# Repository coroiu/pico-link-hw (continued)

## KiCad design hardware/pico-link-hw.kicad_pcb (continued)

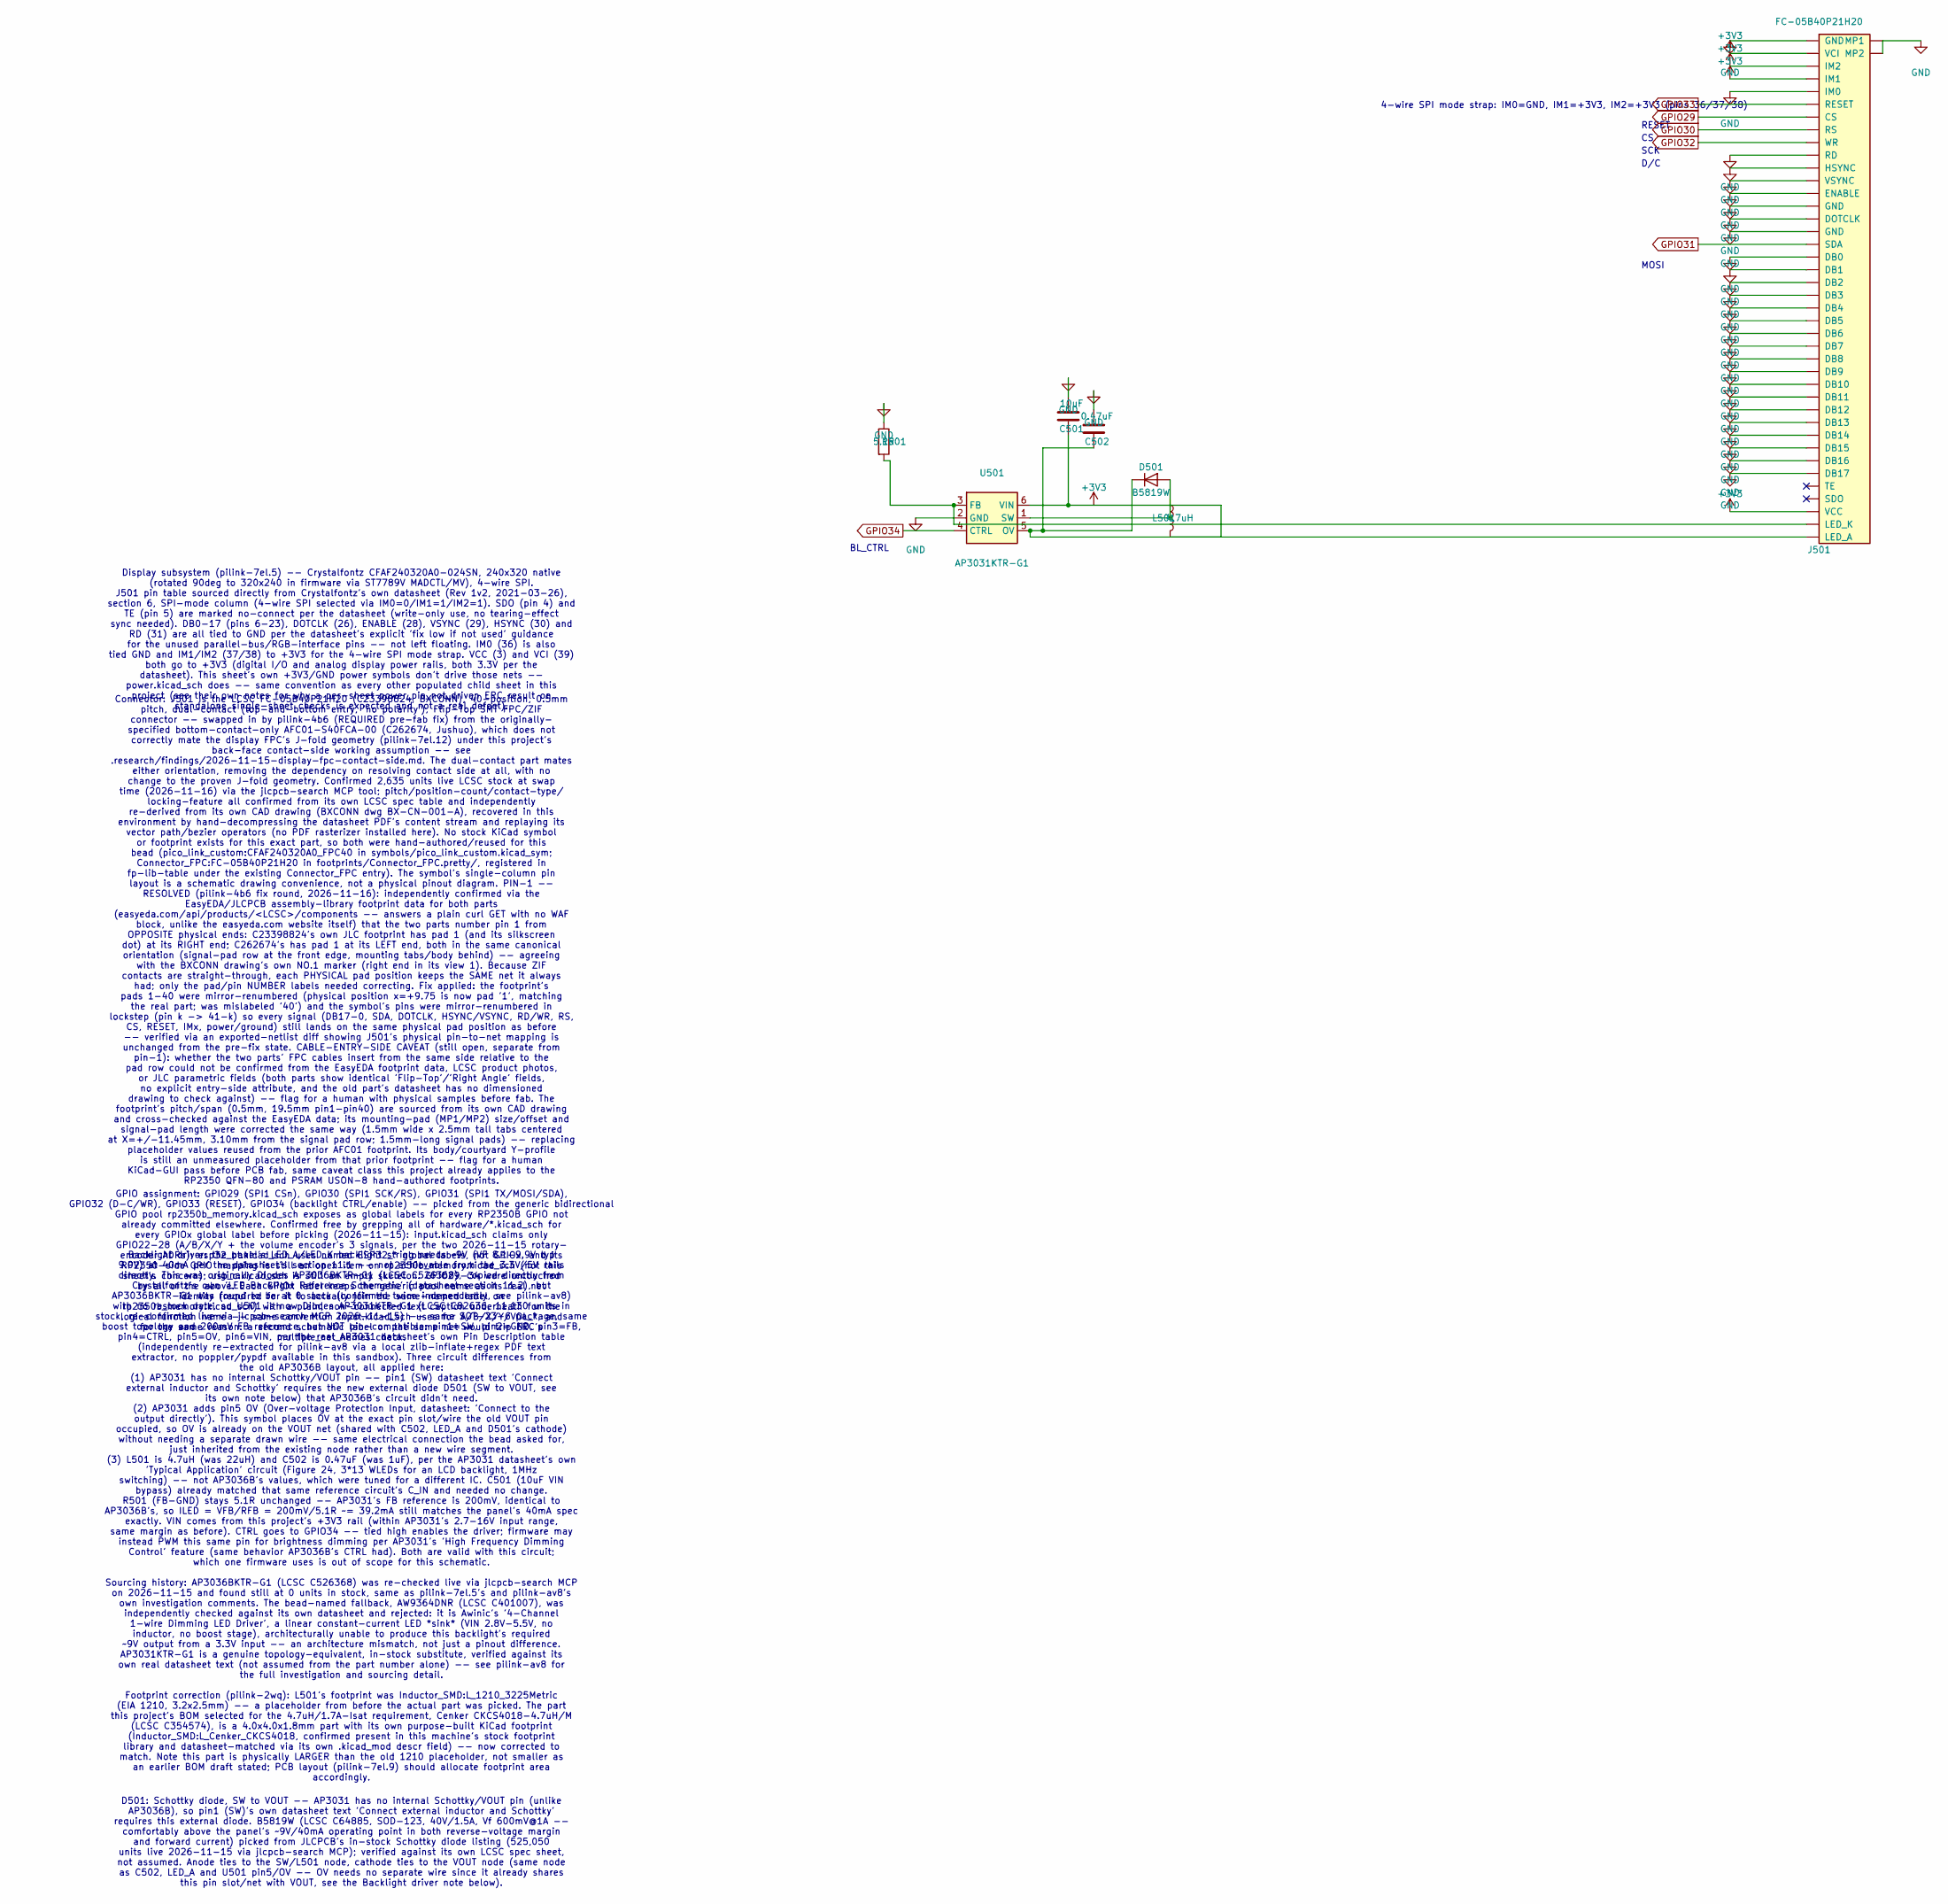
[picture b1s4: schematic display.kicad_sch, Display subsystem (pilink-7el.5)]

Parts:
C501: 10uF; C_0805_2012Metric
C502: 0.47uF; C_0805_2012Metric
D501: B5819W; D_SOD-123
J501: FC-05B40P21H20
L501: 4.7uH; L_Cenker_CKCS4018
R501: 5.1R; R_0402_1005Metric
U501: AP3031KTR-G1; SOT-23-6

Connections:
+3V3: C501.2, J501.2 (VCI), J501.3 (IM2), J501.4 (IM1), J501.38 (VCC), L501.2, U501.6 (VIN); also elsewhere on the board
GND: C501.1, C502.1, J501.1 (GND), J501.5 (IM0), J501.10 (RD), J501.11 (HSYNC), J501.12 (VSYNC), J501.13 (ENABLE), J501.14 (GND), J501.15 (DOTCLK), J501.16 (GND), J501.18 (DB0), J501.19 (DB1), J501.20 (DB2), J501.21 (DB3), J501.22 (DB4), J501.23 (DB5), J501.24 (DB6), J501.25 (DB7), J501.26 (DB8), J501.27 (DB9), J501.28 (DB10), J501.29 (DB11), J501.30 (DB12), J501.31 (DB13), J501.32 (DB14), J501.33 (DB15), J501.34 (DB16), J501.35 (DB17), J501.MP1, J501.MP2, R501.1, U501.2 (GND); also elsewhere on the board
GPIO29: J501.7 (CS); also elsewhere on the board
GPIO30: J501.8 (RS); also elsewhere on the board
GPIO31: J501.17 (SDA); also elsewhere on the board
GPIO32: J501.9 (WR); also elsewhere on the board
GPIO33: J501.6 (RESET); also elsewhere on the board
GPIO34: U501.4 (CTRL); also elsewhere on the board
unnamed: D501.2 (A), L501.1, U501.1 (SW)
unnamed: C502.2, D501.1 (K), J501.40 (LED_A), U501.5 (OV)
unnamed: J501.39 (LED_K), R501.2, U501.3 (FB)

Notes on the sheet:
MOSI
D/C
SCK
RESET
D501: Schottky diode, SW to VOUT -- AP3031 has no internal Schottky/VOUT pin (unlike AP3036B), so pin1 (SW)'s own datasheet text 'Connect external inductor and Schottky' requires this external diode. B5819W (LCSC C64885, SOD-123, 40V/1.5A, Vf 600mV@1A -- comfortably above the panel's ~9V/40mA opera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
BL_CTRL
4-wire SPI mode strap: IM0=GND, IM1=+3V3, IM2=+3V3 (pins 36/37/38)
Display subsystem (pilink-7el.5) -- Crystalfontz CFAF240320A0-024SN, 240x320 native (rotated 90deg to 320x240 in firmware via ST7789V MADCTL/MV), 4-wire SPI. J501 pin table sourced directly from Crystalfontz's own datasheet (Rev 1v2, 2021-03-26), section 6, SPI-mode column (4-wire SPI selected via 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
Connector: J501 is the LCSC FC-05B40P21H20 (C23398824, BXCONN), 40-position, 0.5mm pitch, dual-contact (top-and-bottom entry, 'no polarity'), Flip-Top SMT FPC/ZIF connector -- swapped in by pilink-4b6 (REQUIRED pre-fab fix) from the originally- specified bottom-contact-only AFC01-S40FCA-00 (C262674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
GPIO assignment: GPIO29 (SPI1 CSn), GPIO30 (SPI1 SCK/RS), GPIO31 (SPI1 TX/MOSI/SDA), GPIO32 (D-C/WR), GPIO33 (RESET), GPIO34 (backlight CTRL/enable) -- picked from the generic bidirectional GPIO pool rp2350b_memory.kicad_sch exposes as global labels for every RP2350B GPIO not already committed else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
Backlight driver: the panel's LED_A/LED_K backlight string needs ~9V (VF 8.1-9.9V typ 9.0V) at 40mA per the datasheet's section 11.1 -- not achievable from the 3.3V/5V rails directly. This was originally Diodes AP3036BKTR-G1 (LCSC C526368), copied directly from Crystalfontz's own 'LED Backlight Ref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

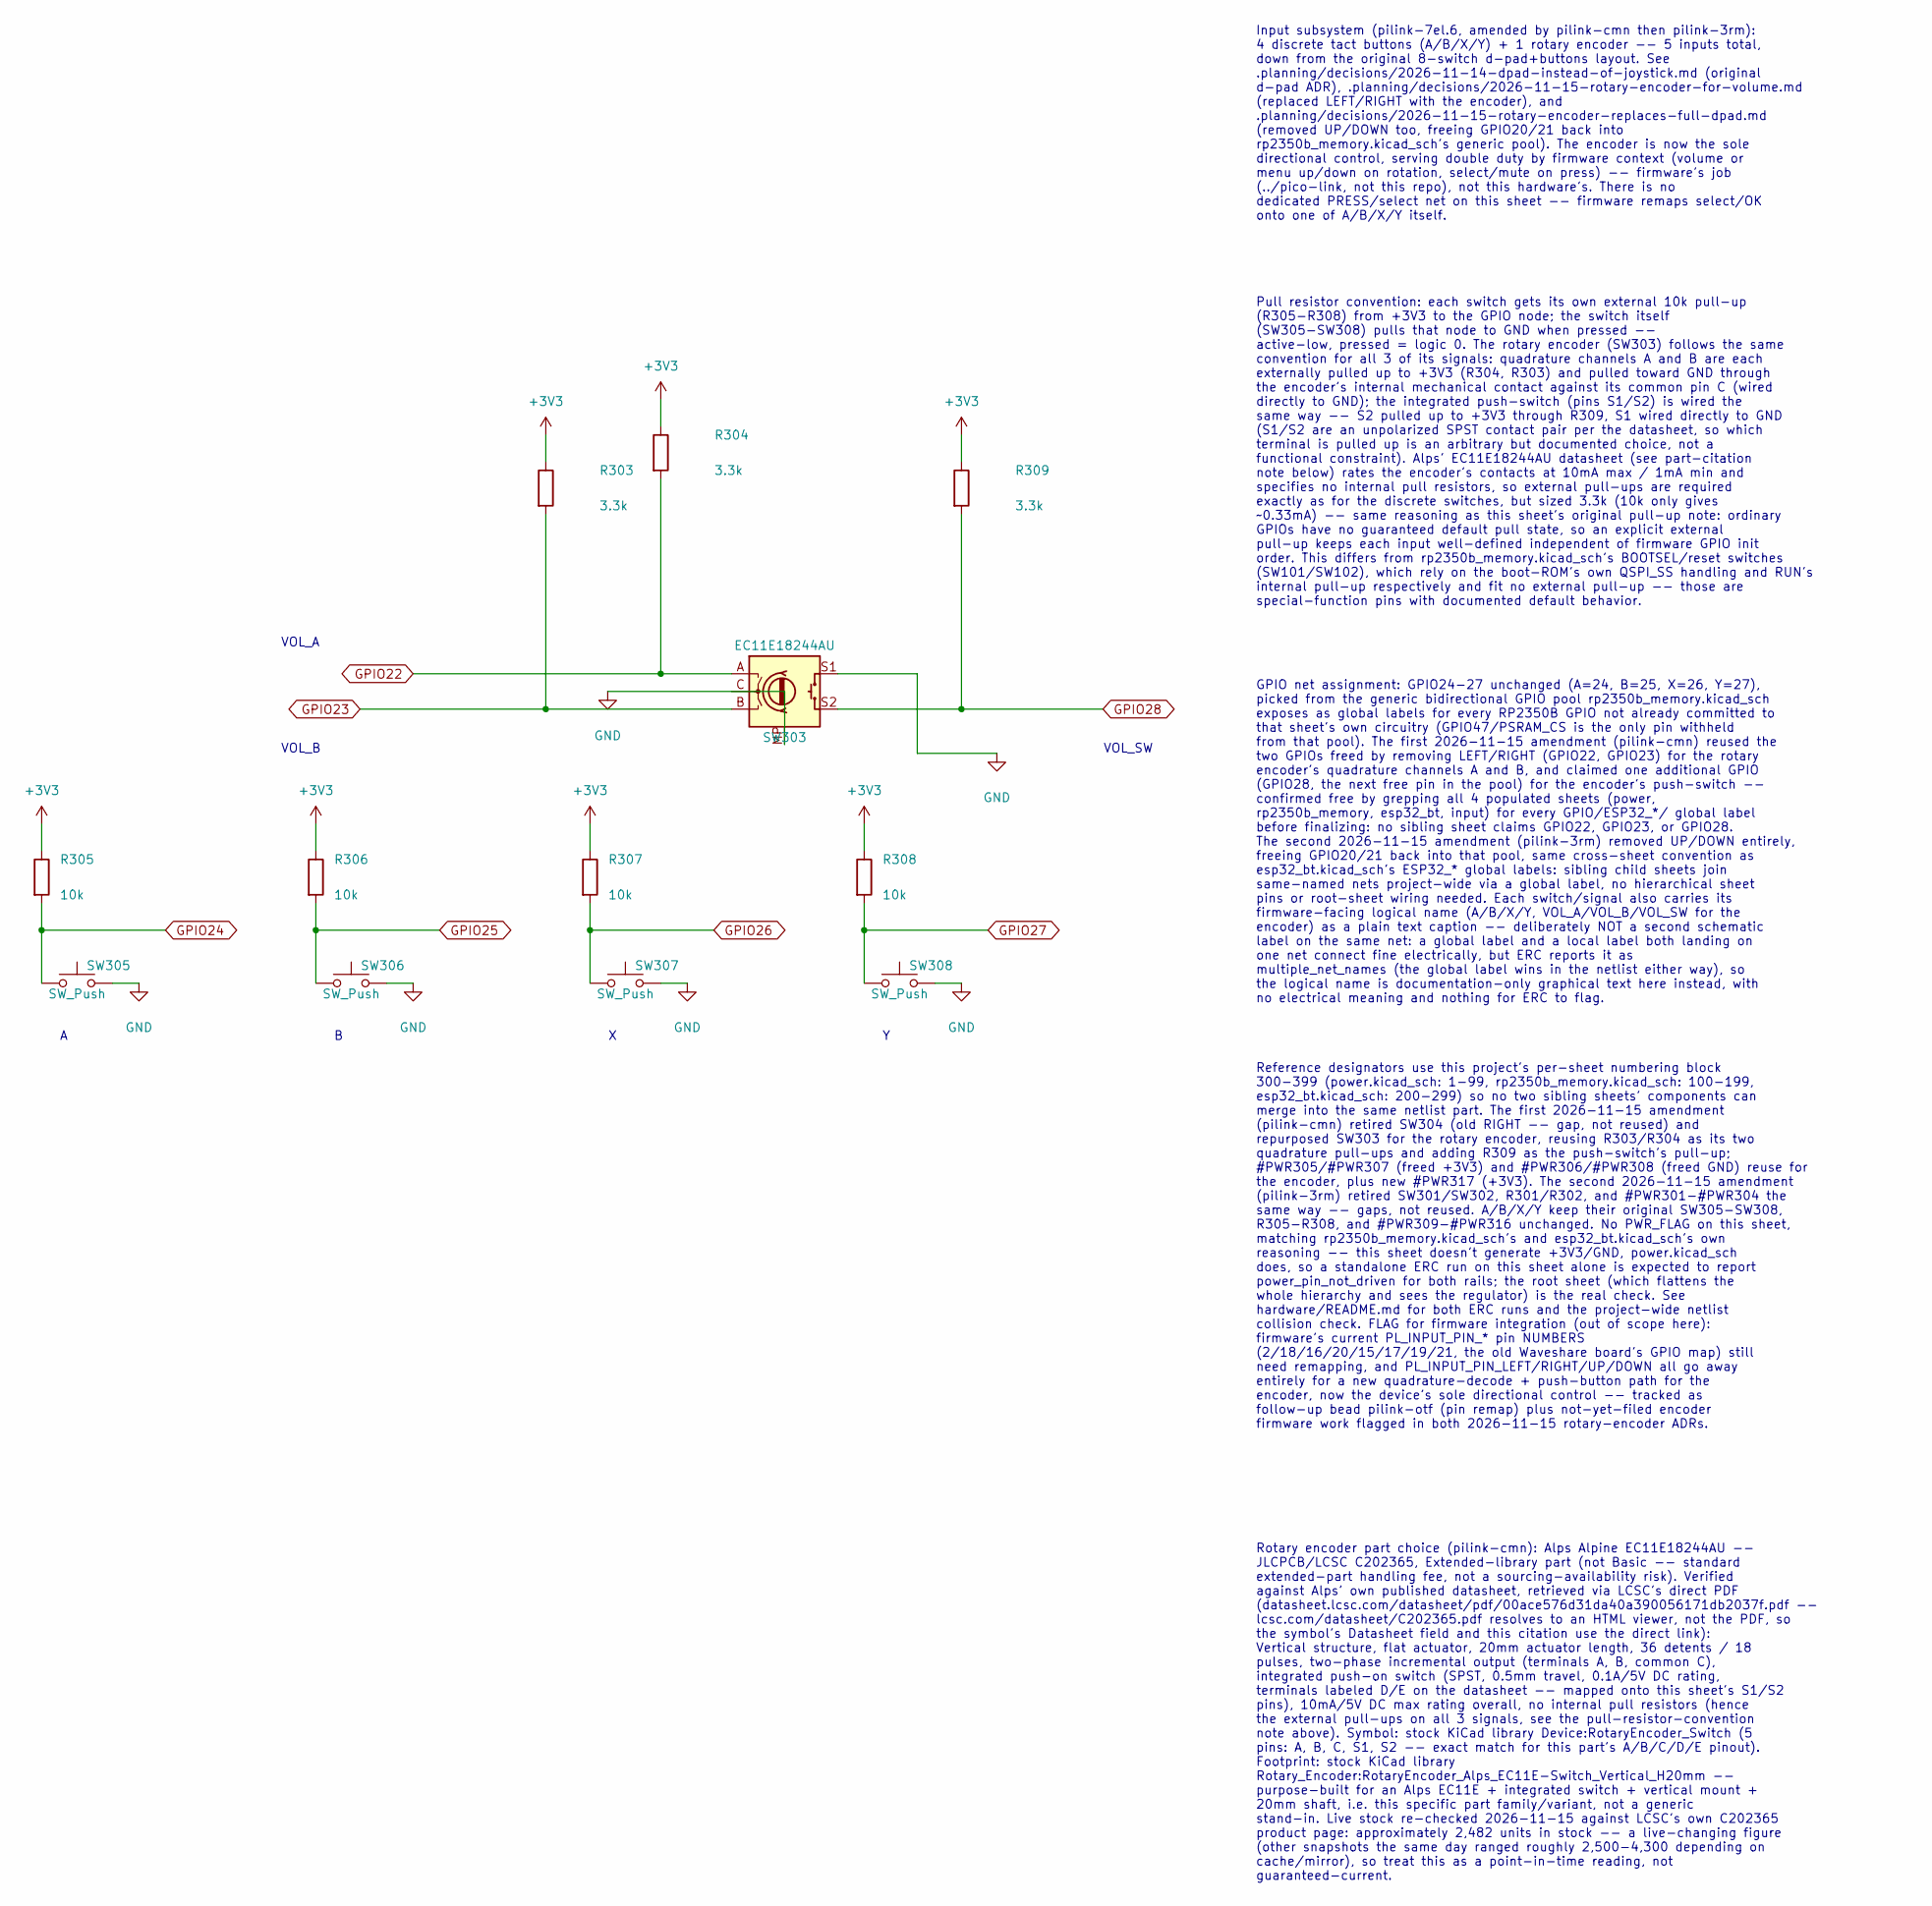
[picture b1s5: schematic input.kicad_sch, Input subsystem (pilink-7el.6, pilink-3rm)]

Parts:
R303, R304, R309: 3.3k; R_0402_1005Metric
R305, R306, R307, R308: 10k; R_0402_1005Metric
SW303: EC11E18244AU; RotaryEncoder_Alps_EC11E-Switch_Vertical_H20mm
SW305, SW306, SW307, SW308: SW_Push; SW_SPST_PTS645

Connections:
+3V3: R303.1, R304.1, R305.1, R306.1, R307.1, R308.1, R309.1; also elsewhere on the board
GND: SW303.C, SW303.MP, SW303.S1, SW305.2, SW306.2, SW307.2, SW308.2; also elsewhere on the board
GPIO22: R304.2, SW303.A; also elsewhere on the board
GPIO23: R303.2, SW303.B; also elsewhere on the board
GPIO24: R305.2, SW305.1; also elsewhere on the board
GPIO25: R306.2, SW306.1; also elsewhere on the board
GPIO26: R307.2, SW307.1; also elsewhere on the board
GPIO27: R308.2, SW308.1; also elsewhere on the board
GPIO28: R309.2, SW303.S2; also elsewhere on the board

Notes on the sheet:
VOL_B
VOL_A
VOL_SW
Input subsystem (pilink-7el.6, amended by pilink-cmn then pilink-3rm): 4 discrete tact buttons (A/B/X/Y) + 1 rotary encoder -- 5 inputs total, down from the original 8-switch d-pad+buttons layout. See .planning/decisions/2026-11-14-dpad-instead-of-joystick.md (original d-pad ADR), .planning/decisio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
Pull resistor convention: each switch gets its own external 10k pull-up (R305-R308) from +3V3 to the GPIO node; the switch itself (SW305-SW308) pulls that node to GND when pressed -- active-low, pressed = logic 0. The rotary encoder (SW303) follows the same convention for all 3 of its signals: quad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
GPIO net assignment: GPIO24-27 unchanged (A=24, B=25, X=26, Y=27), picked from the generic bidirectional GPIO pool rp2350b_memory.kicad_sch exposes as global labels for every RP2350B GPIO not already committed to that sheet's own circuitry (GPIO47/PSRAM_CS is the only pin withheld from that pool). 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
Reference designators use this project's per-sheet numbering block 300-399 (power.kicad_sch: 1-99, rp2350b_memory.kicad_sch: 100-199, esp32_bt.kicad_sch: 200-299) so no two sibling sheets' components can merge into the same netlist part. The first 2026-11-15 amendment (pilink-cmn) retired SW304 (ol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
Rotary encoder part choice (pilink-cmn): Alps Alpine EC11E18244AU -- JLCPCB/LCSC C202365, Extended-library part (not Basic -- standard extended-part handling fee, not a sourcing-availability risk). Verified against Alps' own published datasheet, retrieved via LCSC's direct PDF (datasheet.lcsc.com/d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

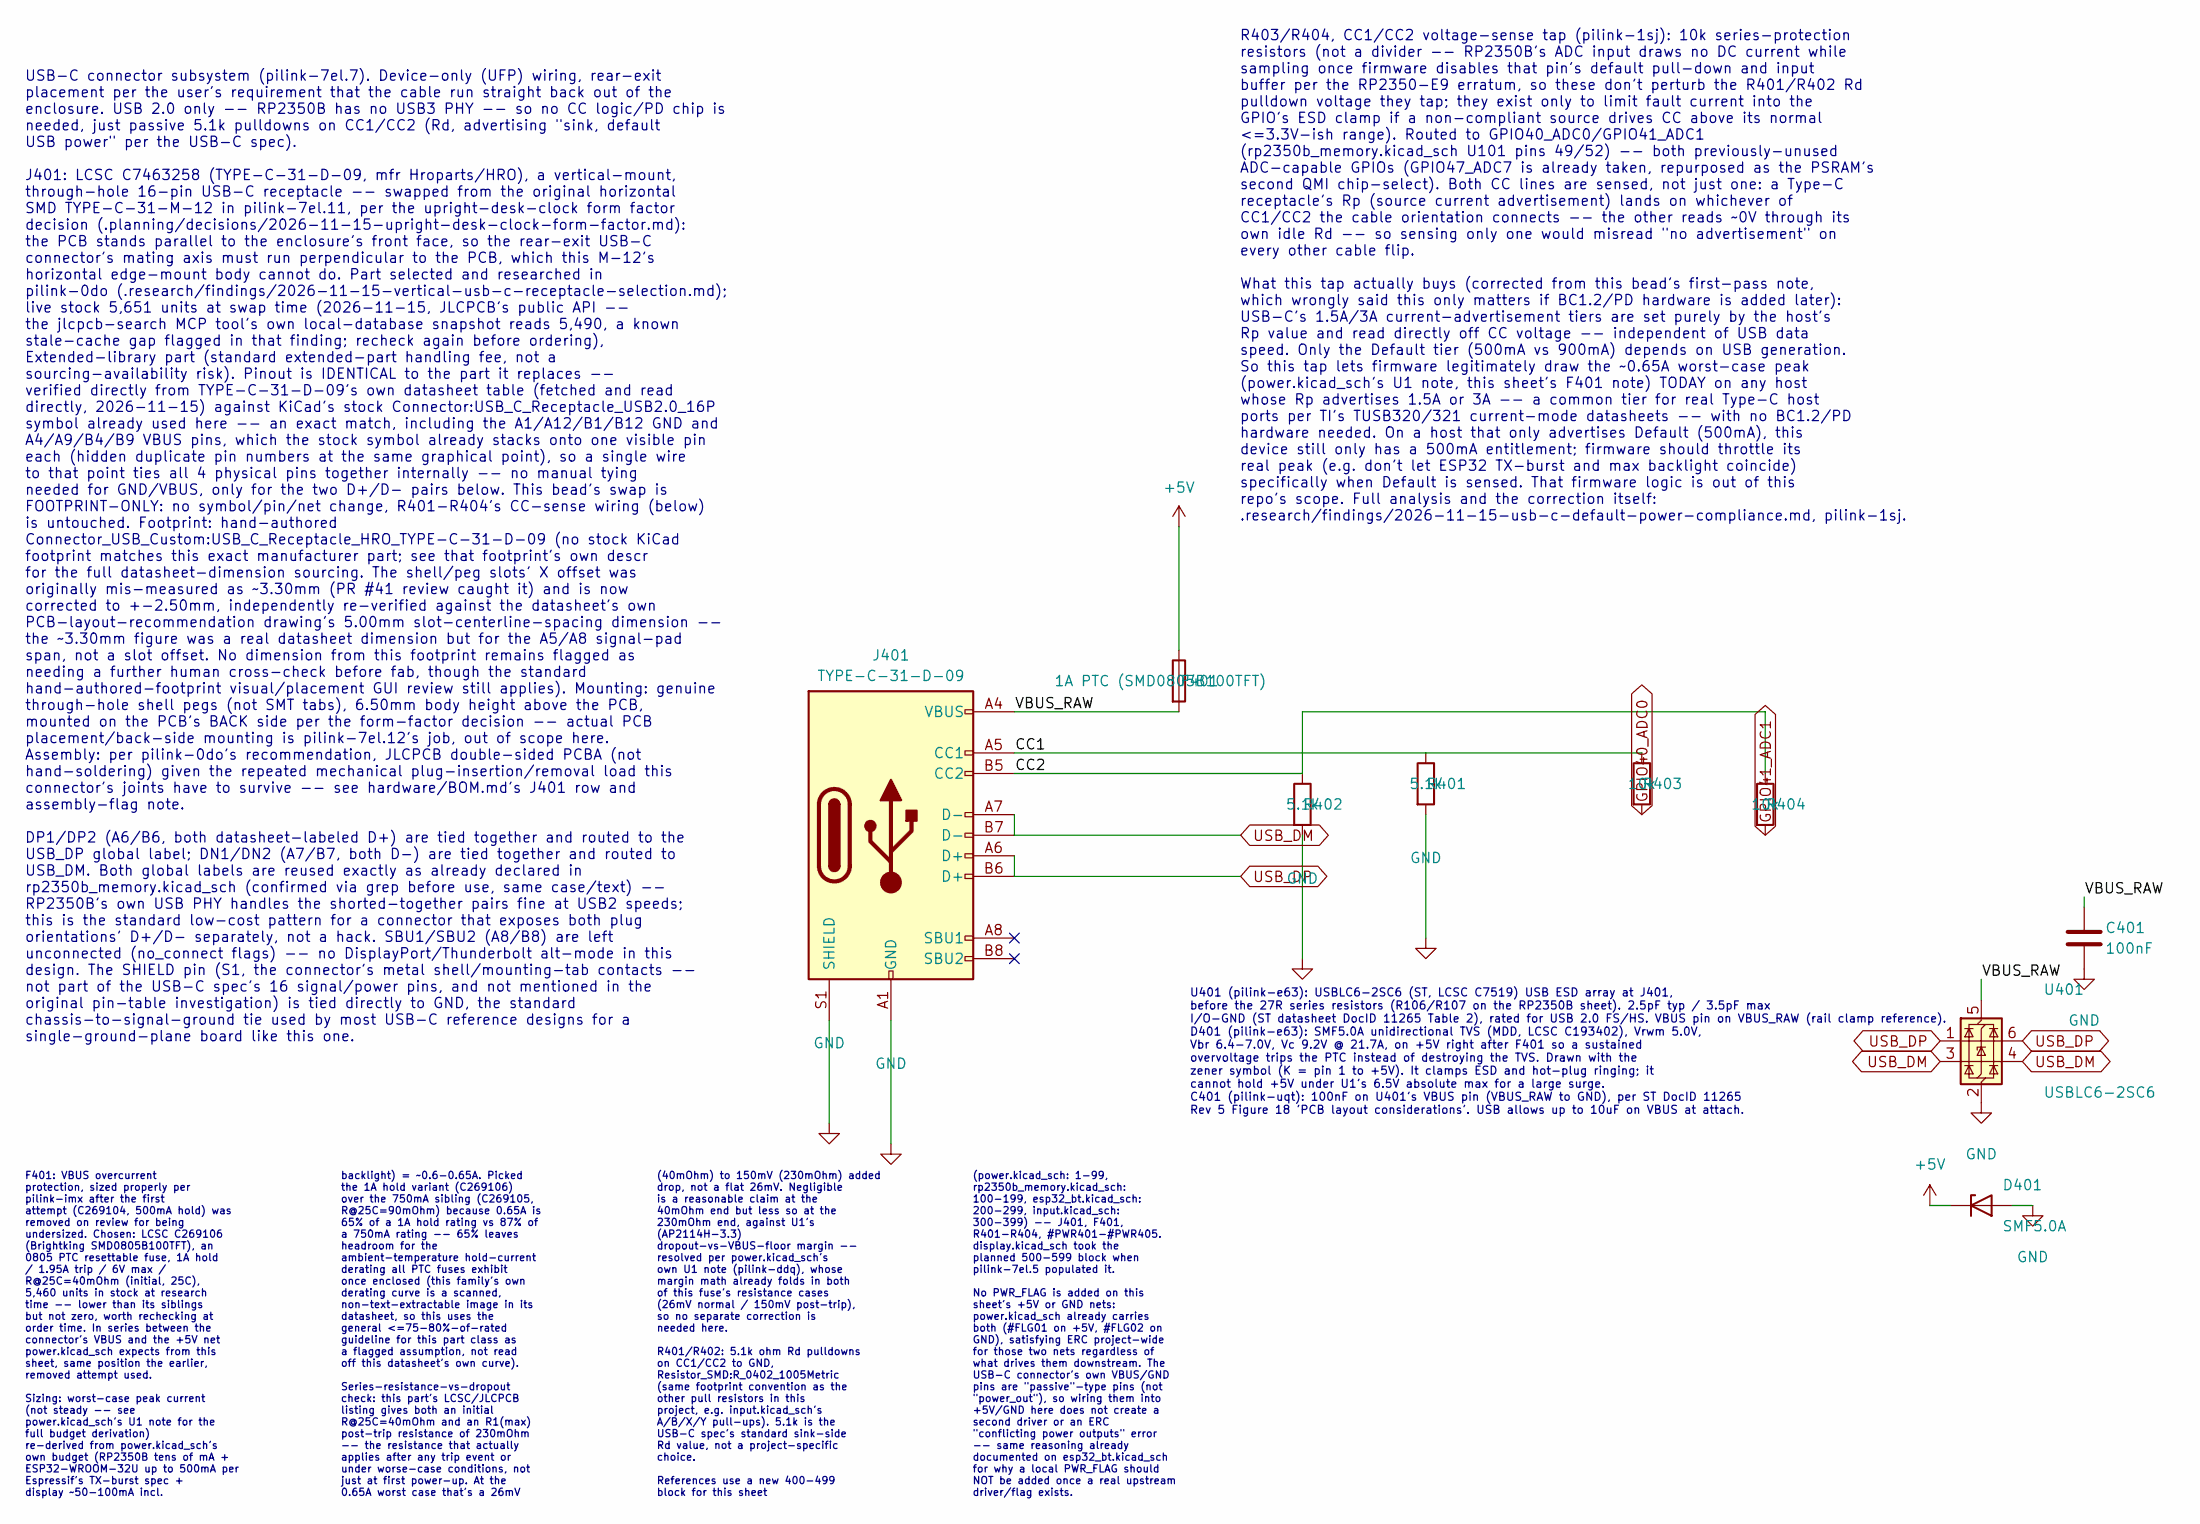
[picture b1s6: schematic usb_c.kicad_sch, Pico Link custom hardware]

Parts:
C401: 100nF; C_0402_1005Metric
D401: SMF5.0A; D_SMF
F401: 1A PTC (SMD0805B100TFT); Fuse_0805_2012Metric
J401: TYPE-C-31-D-09; USB_C_Receptacle_HRO_TYPE-C-31-D-09
R401, R402: 5.1k; R_0402_1005Metric
R403, R404: 10k; R_0402_1005Metric
U401: USBLC6-2SC6; SOT-23-6

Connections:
+5V: D401.1 (K), F401.1; also elsewhere on the board
/USB-C/CC1: J401.A5 (CC1), R401.1, R403.1
/USB-C/CC2: J401.B5 (CC2), R402.1, R404.1
/USB-C/VBUS_RAW: C401.1, F401.2, J401.A4 (VBUS), J401.A9 (VBUS), J401.B4 (VBUS), J401.B9 (VBUS), U401.5 (VBUS)
GND: C401.2, D401.2 (A), J401.A1 (GND), J401.A12 (GND), J401.B1 (GND), J401.B12 (GND), J401.S1 (SHIELD), R401.2, R402.2, U401.2 (GND); also elsewhere on the board
GPIO40_ADC0: R403.2; also elsewhere on the board
GPIO41_ADC1: R404.2; also elsewhere on the board
USB_DM: J401.A7 (D-), J401.B7 (D-), U401.3 (I/O2), U401.4 (I/O2); also elsewhere on the board
USB_DP: J401.A6 (D+), J401.B6 (D+), U401.1 (I/O1), U401.6 (I/O1); also elsewhere on the board

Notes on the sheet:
USB-C connector subsystem (pilink-7el.7). Device-only (UFP) wiring, rear-exit placement per the user's requirement that the cable run straight back out of the enclosure. USB 2.0 only -- RP2350B has no USB3 PHY -- so no CC logic/PD chip is needed, just passive 5.1k pulldowns on CC1/CC2 (Rd, advertis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
F401: VBUS overcurrent protection, sized properly per pilink-imx after the first attempt (C269104, 500mA hold) was removed on review for being undersized. Chosen: LCSC C269106 (Brightking SMD0805B100TFT), an 0805 PTC resettable fuse, 1A hold / 1.95A trip / 6V max / R@25C=40mOhm (initial, 25C), 5,46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
backlight) = ~0.6-0.65A. Picked the 1A hold variant (C269106) over the 750mA sibling (C269105, R@25C=90mOhm) because 0.65A is 65% of a 1A hold rating vs 87% of a 750mA rating -- 65% leaves headroom for the ambient-temperature hold-current derating all PTC fuses exhibit once enclosed (this family's 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
(40mOhm) to 150mV (230mOhm) added drop, not a flat 26mV. Negligible is a reasonable claim at the 40mOhm end but less so at the 230mOhm end, against U1's (AP2114H-3.3) dropout-vs-VBUS-floor margin -- resolved per power.kicad_sch's own U1 note (pilink-ddq), whose margin math already folds in both of 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
(power.kicad_sch: 1-99, rp2350b_memory.kicad_sch: 100-199, esp32_bt.kicad_sch: 200-299, input.kicad_sch: 300-399) -- J401, F401, R401-R404, #PWR401-#PWR405. display.kicad_sch took the planned 500-599 block when pilink-7el.5 populated it. No PWR_FLAG is added on this sheet's +5V or GND nets: power.k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
R403/R404, CC1/CC2 voltage-sense tap (pilink-1sj): 10k series-protection resistors (not a divider -- RP2350B's ADC input draws no DC current while sampling once firmware disables that pin's default pull-down and input buffer per the RP2350-E9 erratum, so these don't perturb the R401/R402 Rd pulldow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
U401 (pilink-e63): USBLC6-2SC6 (ST, LCSC C7519) USB ESD array at J401, before the 27R series resistors (R106/R107 on the RP2350B sheet). 2.5pF typ / 3.5pF max I/O-GND (ST datasheet DocID 11265 Table 2), rated for USB 2.0 FS/HS. VBUS pin on VBUS_RAW (rail clamp reference). D401 (pilink-e63): SMF5.0A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

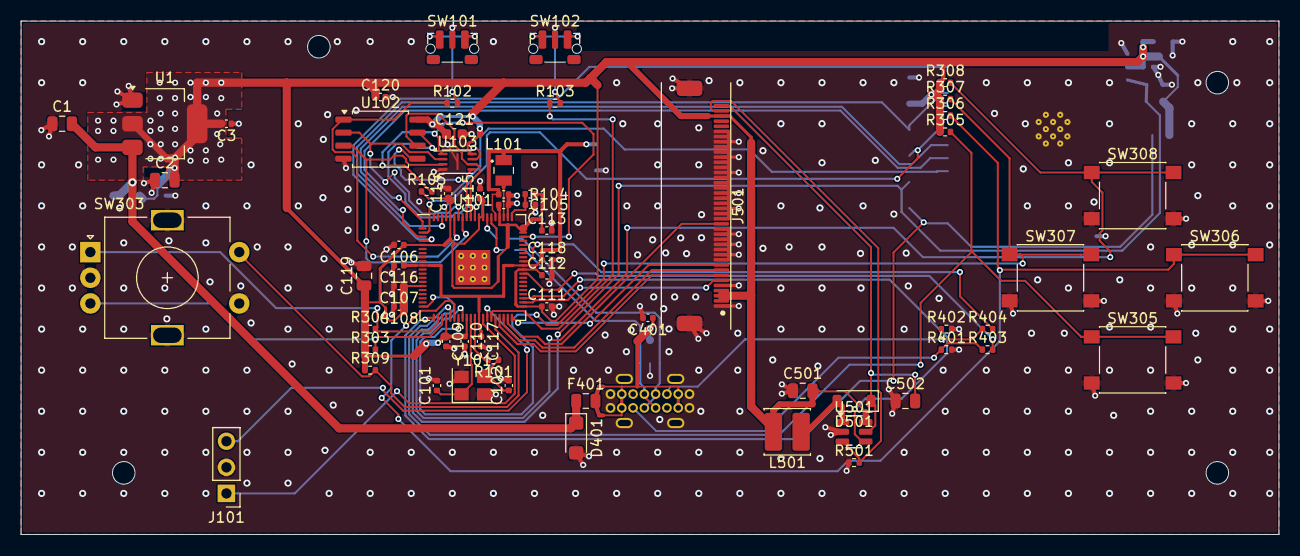
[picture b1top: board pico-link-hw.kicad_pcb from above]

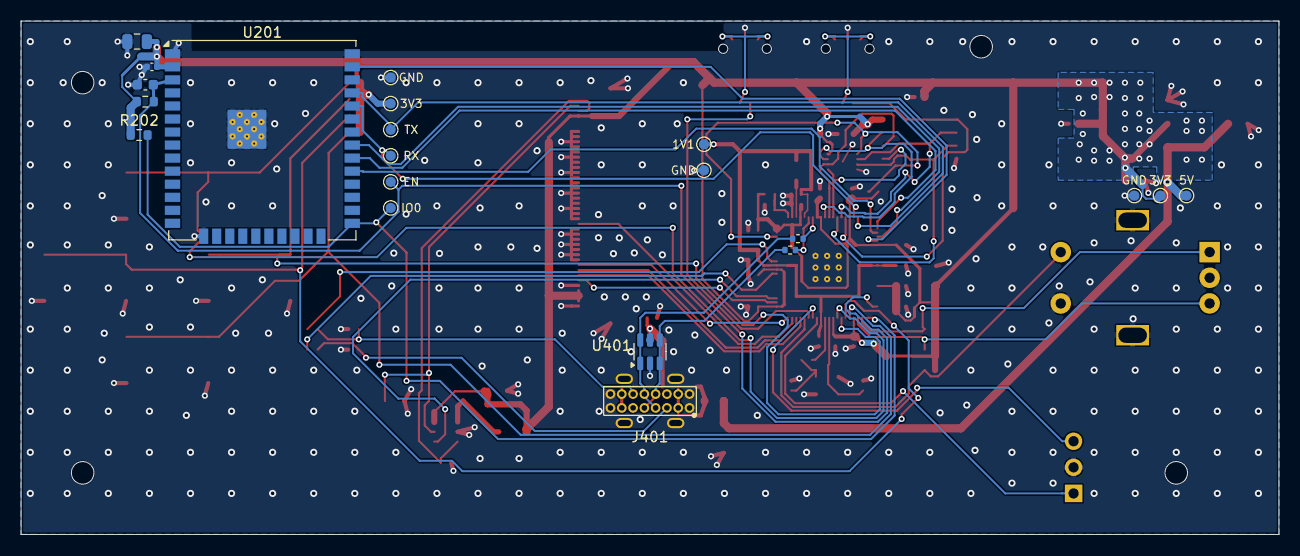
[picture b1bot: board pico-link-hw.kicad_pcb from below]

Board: 2 copper layers, 122.5 x 50.0 mm, 89 parts (21 on the bottom side), 54 nets.

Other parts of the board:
H1, H2, H3, H4: MountingHole_M2

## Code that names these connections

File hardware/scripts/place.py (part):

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    "C115": (CX + 0.7, CY - RING, "chip"),
    # pilink-2x7 (RP2350 DS 6.3.8.1 / Fig. 26): the VREG stack above pins
    # 65..61 (FB, VIN, LX, PGND, AVDD, x 46.2..47.8). C103 (C_IN) right above
    # the pins and C104 (C_OUT) above it both straddle the VREG_LX column
    # (pin 63, x 47.0): west pad (+3V3 / +1V1) over VIN/FB, east pad (GND)
    # over PGND, so the VIN -> C_IN -> PGND loop is ~1mm and LX runs up
    # between the pads. L101 (pilink-7sb: Abracon AOTA-B201610, 2.0 x 1.6mm,
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    # --- USB-C protection and termination (pilink-audit-a) -------------------
    # pilink-e63: U401 (USBLC6-2SC6) on B.Cu right above J401 (courtyards
    # touch, no overlap), rot 90 so D-/D+ flow straight through it north-south:
    # west column pins 3/4 = USB_DM (from J401 B7), east column 1/6 = USB_DP
    # (from B6), GND (pin 2) on the J401 side, VBUS (pin 5) away from it.
    "U401": (61.25, 32.2, 90),
    # pilink-uqt: C401 100nF on U401's VBUS pin (ST DocID 11265 Fig. 18), on
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    # as of pilink-2yw; this bead's own job was restoring the DIAMOND to
    # y=25 too (see below) without re-opening the knob's own placement.
    "SW303": (6.75, 22.5, 0),  # pilink-4qc: shaft x 14.25 = 61.25 - 47.0, mirror of the diamond centre x=108.25
    "R304": (34.0, 30.0, 0),   # encoder A pull-up (GPIO22)
    "R303": (34.0, 32.0, 0),   # encoder B pull-up (GPIO23)
    "R309": (34.0, 34.0, 0),   # encoder push-switch pull-up (GPIO28)
    # A/B/X/Y diamond, button zone (x>86): caps Ø8mm, +/-8mm centres,
    # standard gamepad layout (Y top/X left/B right/A bottom), matching the
    # proposal's own diagram annotation order. The exact SW305-308 <->
    # physical-position mapping is a layout choice, not schematic-
    # constrained (firmware maps GPIO24-27 to logical buttons separately,
    # see pilink-otf); documented here, not inferred.
    # pilink-2yw shifted the whole group DOWN 9mm as a rigid block, centre
    # (102,25) -> (102,34), to open enough clear height above it for U201's
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             "TP201", "TP202", "TP203", "TP204", "TP205", "TP206"}

# pilink-brf: B.SilkS signal names beside the test pads (board-level text,
# removed and re-added on every run). (ref, label, dx, dy) from the pad.
TP_LABELS = [("TP201", "GND", -2.0, 0), ("TP202", "3V3", -2.0, 0),
             ("TP203", "TX", -2.0, 0), ("TP204", "RX", -2.0, 0),
             ("TP205", "EN", -2.0, 0), ("TP206", "IO0", -2.0, 0),
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
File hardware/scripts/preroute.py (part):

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    B.Cu from B7/B6 through U401's flow-through pad pair (ESD), north and
    then as a 45-degree parallel pair to R106/R107 (27R, B.Cu under U101),
    and from the resistor to a via at pin 66/67 (the MCU-side nets
    USB_DM_MCU / USB_DP_MCU). U401's GND and VBUS pins get their own vias.
  * U201 decoupling / EN (pilink-fvz): pin 2 -> C202 -> C201, pin 3 ->
    C203 -> R201, two GND vias, all B.Cu.
  * +3V3 trunk (pilink-yt5): 0.8mm F.Cu from U1's tab to two vias at C202,
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LX_NET = "/RP2350B + Memory/VREG_LX"
AVDD_NET = "/RP2350B + Memory/VREG_AVDD"
PSRAM_CS = "/RP2350B + Memory/PSRAM_CS"
GPIO41 = "GPIO41_ADC1"
QSPI_NETS = ["/RP2350B + Memory/" + n for n in
             ("QSPI_SCLK", "QSPI_SD0", "QSPI_SD1", "QSPI_SD2", "QSPI_SD3", "QSPI_SS")]
# pilink-audit-a: USB MCU-side nets (U101 <-> R106/R107), the U401 VBUS via,
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PREROUTE_NETS = ["USB_DP", "USB_DM", DP_MCU, DM_MCU, VBUS, "/USB-C/CC2",
                 XIN, XOUT, LED_K, LED_A,
                 BOOT_NET, RESET_NET, "GND", "+1V1", "+3V3", "ESP32_EN",
                 LX_NET, AVDD_NET, PSRAM_CS, GPIO41] + QSPI_NETS


def main():
    board = pcbnew.LoadBoard(BOARD)
    for t in list(board.GetTracks()):
        # VREG_LX (pin 63 -> L101 pad 1) is wholly this script's, so router
        # copper on it goes too: a router stub into the old, larger L101 pad
        # was left dangling when L101 changed (pilink-7sb)
        if (t.IsLocked() and t.GetNetname() in PREROUTE_NETS) or t.GetNetname() == LX_NET:
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    yl = yi + 0.36
    path("+3V3", F, [(x64, y64), (x64, yl), (x60i - 0.31, yl), (x60i, y60)], width=0.25)
    path("+3V3", F, [(x60i, y60), (x60, y60)], width=0.2)
    # The DVDD run boxes in pins 52..60 on F.Cu (any F.Cu path from the VREG
    # node to a +1V1 pin does). Of those only PSRAM_CS (58) and GPIO41 (52)
    # have to get out: each drops through a via right beside the pins and
    # crosses under the caps column and the DVDD run on B.Cu to a via east
    # of it (~3.5mm of B.Cu each), where the router picks it up. Their
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    # PSRAM_CS on to U103 (pilink-93a), locked, ~33mm: from the hop's east
    # via up F.Cu east of the DVDD run (round TP101's +1V1 via), west on
    # F.Cu over the VREG block (north of the +1V1 run, south of R102/R103),
    # then one short B.Cu hop under QSPI_SCLK into U103 pin 1. Left to the
    # router it ran on B.Cu under pins 61-70 (cutting the B.Cu under the
    # regulator off from the EP's) or, with that strip kept out
    # (plane_keepout VREG_PINS_B), under the exposed pad or ~70mm round the
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    path(AVDD_NET, F, [(x61, y61), (x61, yo), (x61 + 0.3, yo - 0.3),
                       (c5_1[0], yo - 0.3), c5_1], width=0.2)
    path(AVDD_NET, F, [r4_2, c5_1], width=0.25)
    # R104's +3V3 end: the DVDD run, L101 and the pins box it in on F.Cu,
    # and the B.Cu under the block is plane (plane_keepout.py), so the
    # router can only rarely get it out. Take it straight down past C105's
    # east end into C113.1 (+3V3, the pin 60 decoupler just below).
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
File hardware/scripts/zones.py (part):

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FAST_NETS = (["USB_DP", "USB_DM", "/RP2350B + Memory/USB_DP_MCU",
              "/RP2350B + Memory/USB_DM_MCU", "/RP2350B + Memory/PSRAM_CS"]
             + ["/RP2350B + Memory/QSPI_" + n for n in ("SCLK", "SD0", "SD1", "SD2", "SD3", "SS")]
             + ["GPIO29", "GPIO30", "GPIO31", "GPIO32", "GPIO33"])


def spreader_outline():
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
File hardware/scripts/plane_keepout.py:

"""Ground-plane keepouts (pilink-r1h, pilink-2x7). Library, not run directly.

Both layers carry signals and GND pours (Freerouting would not keep B.Cu
free with this placement, see route.py). Two kinds of rule area keep the
B.Cu plane whole where it matters most:

* add_plane_keepouts() / remove_plane_keepouts(): B.Cu track keepouts that
  route.py exports to Freerouting (and removes again before saving), so
  no signal runs on B.Cu
    - under the VREG hot loop and from there under U101's top pin row down
      to the exposed pad (RP2350 DS 6.3.8.1: "the bottom layer under the
      regulator is a ground plane that connects to the QFN GND central
      pad"; pilink-93a),
    - under the crystal (Y101, its load caps and R101),
    - two channels from the exposed pad to the east and south decouplers'
      GND vias (EP_E / EP_S, pilink-xy5),
    - under U201's module body, where signal vias are kept out too
      (NOVIA_B, pilink-9on).
  Vias stay allowed (GND fan-out / stitching vias are plane, not signal).
  Each area is cut back LOCKED_GAP from locked B.Cu tracks (the QSPI
  pre-route runs on B.Cu under U101): Freerouting does not finish when a
  keepout overlaps fixed wiring.
  Not under U101: any B.Cu keepout there, even one only over the exposed
  pad, made Freerouting run on without finishing in every trial (the
  chip's inner pin fan-out needs B.Cu; the narrower EP_E / EP_S channels,
  which reach under the body only beside spare or B.Cu-free pins, do
  route), so whether the exposed pad's vias
  land on the main B.Cu plane is up to the routing; zones.py's gate checks
  that they at least join the main ground.
* add_pour_keepouts(): F.Cu no-fill areas zones.py adds, so the GND pour
  does not reach the VREG high-current ground island (PGND + C103.2 +
  C104.2, which must meet the main ground at its own two vias only) or the
  area between U101's pin ring and its exposed pad (where it would tie
  PGND's inner end straight to the EP).
Boxes are board-local mm (x0, y0, x1, y1); polygons are point lists.
"""
import pcbnew

O = 100.0          # keep in sync with place.py ORIGIN
NAME_B = "KO_PLANE_B_"
NAME_F = "KO_POUR_F_"
# VREG block: L101, C103/C104/C105, R104, the island vias, FB and the +1V1
# link (place.py / preroute.py geometry)
VREG_B = [(45.4, 10.8), (51.6, 10.8), (51.6, 19.3), (45.4, 19.3)]
# the same plus a channel under pins 68-71 down to the exposed pad's top
# edge, between the QSPI pre-route's B.Cu vias (x <= 43.4) and the USB
# R106/R107 corner (x >= 45.4), so the plane under the regulator meets the
# plane under the EP directly (RP2350 DS 6.3.8.1)
VREG_EP_B = [(45.4, 10.8), (51.6, 10.8), (51.6, 19.3), (45.0, 19.3), (45.0, 22.4),
             (43.7, 22.4), (43.7, 18.9), (45.4, 18.9)]
# What the router can live with: the hot loop only -- C103 (C_IN), C104
# (C_OUT), the PGND island and its two vias, from L101's bottom edge (the
# B.Cu under L101 itself is l101_keepout.py's) down to the pin ring. VREG_B
# and VREG_EP_B also close the B.Cu corridor between L101 and the pins that
# the ESP32 UART nets (U101 pins 1-4 -> U201) need: Freerouting then left
# ESP32_HCI_RXD/TXD/RTS/CTS unrouted on every seed tried.
VREG_LOOP_B = [(45.4, 16.3), (48.8, 16.3), (48.8, 19.3), (45.4, 19.3)]
# pilink-93a: the hot loop plus the strip under U101's top pin row from the
# QSPI pre-route's B.Cu (x <= 43.4) to east of pin 58/C105, down to the
# exposed pad's top edge. Without it the router ran PSRAM_CS on B.Cu along
# y 19.6 under pins 61-70, which cut the B.Cu under the regulator off from
# the EP's (DS 6.3.8.1: "the bottom layer under the regulator is a ground
# plane that connects to the QFN GND central pad"); the regulator's ground
# then reached the EP ~100mm round by copper. Unlike VREG_B / VREG_EP_B it
# leaves the B.Cu between L101 and the pins open for the router.
VREG_PINS_B = [(45.4, 16.3), (48.8, 16.3), (48.8, 19.3), (51.6, 19.3), (51.6, 22.3),
               (43.7, 22.3), (43.7, 19.3), (45.4, 19.3)]
CRYSTAL_B = [(39.5, 32.0), (48.6, 32.0), (48.6, 38.0), (39.5, 38.0)]
# pilink-xy5: channels from U101's exposed pad (x 42.3-45.7, y 22.3-25.7)
# to the GND vias of the decouplers east and south of the chip, so their
# B.Cu reaches the EP directly instead of the long way round (C111/C112/
# C118 ~25mm, C109/C110/C117 44-48mm on the pilink-93a routing; the east
# pin row's and the south row's B.Cu escapes, the +5V run under the south
# pin row and the USB pair boxed their vias in).
#  * EP_E: from the EP's east edge under the spare east-row pins (45-48,
#    GPIO35-38) to C112's fan-out via (gnd_fanout.PREFER, west of the USB
#    pair) and C111's two vias. The USB pair's D- diagonal is cut out
#    (_minus_locked). C118's GND pad reaches C112's by a locked F.Cu link.
#  * EP_S: a strip under the south row's pins 29-32 (+3V3, XIN, XOUT,
#    +1V1: none of them needs B.Cu) down to a band under the C109/C110/C117
#    GND vias, which meets the crystal area (CRYSTAL_B) below.
EP_E_B = [(45.6, 24.9), (51.9, 24.9), (53.6, 26.6), (53.6, 29.1), (51.0, 29.1),
          (51.0, 26.7), (45.6, 26.7)]
EP_S_B = [(43.3, 25.5), (44.9, 25.5), (44.9, 31.0), (46.3, 31.0), (46.3, 32.6),
          (41.6, 32.6), (41.6, 31.0), (43.3, 31.0)]
PLANE_B = {"VREG": VREG_PINS_B, "XTAL": CRYSTAL_B, "EP_E": EP_E_B, "EP_S": EP_S_B}
# pilink-9on: no signal track or via under U201's module body (the ESP32 is
# on B.Cu): the module's underside has its own exposed GND pad, and copper
# under it can be neither inspected nor reworked. The box is the body
# (board x 91.2-106.8, y 3-20) inset to stay clear of the castellated pad
# rows (x <= 91.0 / >= 107.0, bottom row y >= 20.2), so tracks still reach
# every pad from outside. GND copper (fan-out stubs, stitching) is not
# routed by Freerouting and stays allowed.
NOVIA_B = {"U201": [(91.4, 3.0), (106.6, 3.0), (106.6, 19.8), (91.4, 19.8)]}
# F.Cu no-fill: the VREG ground island (FB's west edge to the island vias'
# east edge, L101's pad 1 down to just above the pins) and U101's inside
VREG_F = [(45.75, 16.0), (48.75, 16.0), (48.75, 18.66), (45.75, 18.66)]
U101_F = [(39.4, 19.4), (48.6, 19.4), (48.6, 28.6), (39.4, 28.6)]
POUR_F = {"VREG": VREG_F, "U101": U101_F}


def _poly(pts):
    sp = pcbnew.SHAPE_POLY_SET()
    sp.NewOutline()
    for x, y in pts:
        sp.Append(pcbnew.FromMM(O + x), pcbnew.FromMM(O + y))
    return sp


def _minus_locked(board, sp, layer):
    """sp less the locked (pre-routed) non-GND tracks on `layer`, grown by
    LOCKED_GAP. Freerouting never finishes when a keepout overlaps fixed
    wiring (the QSPI pre-route runs on B.Cu under U101): it keeps trying to
    clear the violation. Each resulting piece is returned hole-free."""
    cut = pcbnew.SHAPE_POLY_SET()
    for t in board.GetTracks():
        if (t.Type() == pcbnew.PCB_TRACE_T and t.IsLocked() and t.GetLayer() == layer
                and t.GetNetname() != "GND"):
            t.TransformShapeToPolygon(cut, layer, pcbnew.FromMM(LOCKED_GAP), 5000,
                                      pcbnew.ERROR_OUTSIDE)
    out = pcbnew.SHAPE_POLY_SET(sp)
    if cut.OutlineCount():
        out.BooleanSubtract(cut)
    out.Fracture()
    return out


LOCKED_GAP = 0.3     # keepout edge to a locked track's edge, mm


def _area(board, name, layer, pts, tracks, fill, avoid_locked=False, vias=False):
    sp = _poly(pts)
    if avoid_locked:
        sp = _minus_locked(board, sp, layer)
    for i in range(sp.OutlineCount()):
        src = sp.Outline(i)
        if src.PointCount() < 3:
            continue
        z = pcbnew.ZONE(board)
        z.SetLayer(layer)
        z.SetIsRuleArea(True)
        z.SetZoneName(name if sp.OutlineCount() == 1 else f"{name}_{i}")
        z.SetDoNotAllowTracks(tracks)
        z.SetDoNotAllowVias(vias)
        z.SetDoNotAllowZoneFills(fill)
        z.SetDoNotAllowPads(False)
        z.SetDoNotAllowFootprints(False)
        o = z.Outline()
        o.NewOutline()
        for j in range(src.PointCount()):
            o.Append(src.CPoint(j))
        board.Add(z)


def remove_plane_keepouts(board):
    for z in list(board.Zones()):
        if z.GetZoneName().startswith(NAME_B):
            board.Remove(z)


def add_plane_keepouts(board):
    remove_plane_keepouts(board)
    for tag, pts in PLANE_B.items():
        _area(board, NAME_B + tag, pcbnew.B_Cu, pts, True, False, avoid_locked=True)
    for tag, pts in NOVIA_B.items():
        _area(board, NAME_B + tag, pcbnew.B_Cu, pts, True, False, avoid_locked=True, vias=True)


def add_pour_keepouts(board):
    for z in list(board.Zones()):
        if z.GetZoneName().startswith(NAME_F):
            board.Remove(z)
    for tag, pts in POUR_F.items():
        _area(board, NAME_F + tag, pcbnew.F_Cu, pts, False, True)
